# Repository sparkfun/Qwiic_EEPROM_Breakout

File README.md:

Qwiic EEPROM - 512Kbit
=======================================

[*Qwiic EEPROM - 512Kbit (COM-18355)*](https://www.sparkfun.com/products/18355)

A simple breakout for the 512kbit common I2C EEPROMs.

Repository Contents
-------------------

* **/Hardware** - Eagle design files (.brd, .sch)
* **/Firmware** - EEPROM test sketch

Documentation
------------

* **[SparkFun External EEPROM Arduino Library](https://github.com/sparkfun/SparkFun_External_EEPROM_Arduino_Library)** - Arduino library for the Qwiic EEPROM - 512Kbit
* **[Qwiic EEPROM Python Package](https://github.com/sparkfun/Qwiic_EEPROM_Py)** - Python package for the Qwiic EEPROM - 512Kbit
* **[Datasheet CAT24C512](https://www.onsemi.com/pub/Collateral/CAT24C512-D.PDF)** - Datasheet for EEPROM part number 24512A
<!-- * **[Datasheet RM24C512C](https://cdn.sparkfun.com/assets/2/c/4/c/0/DS-RM24C512C_082.pdf)** - Datasheet for EEPROM part number 24512C -->
* **[Reading and Writing Serial EEPROMs](https://learn.sparkfun.com/tutorials/reading-and-writing-serial-eeproms)** - Tutorial
* **[Qwiic EEPROM Hookup Guide](https://learn.sparkfun.com/tutorials/1661)** - Hookup guide for the Qwiic EEPROM - 512Kbit

License Information
-------------------

This product is _**open source**_! 

Please review the LICENSE.md file for license information. 

If you have any questions or concerns on licensing, please contact technical support on our [SparkFun forums](https://forum.sparkfun.com/viewforum.php?f=152).

Distributed as-is; no warranty is given.

- Your friends at SparkFun.

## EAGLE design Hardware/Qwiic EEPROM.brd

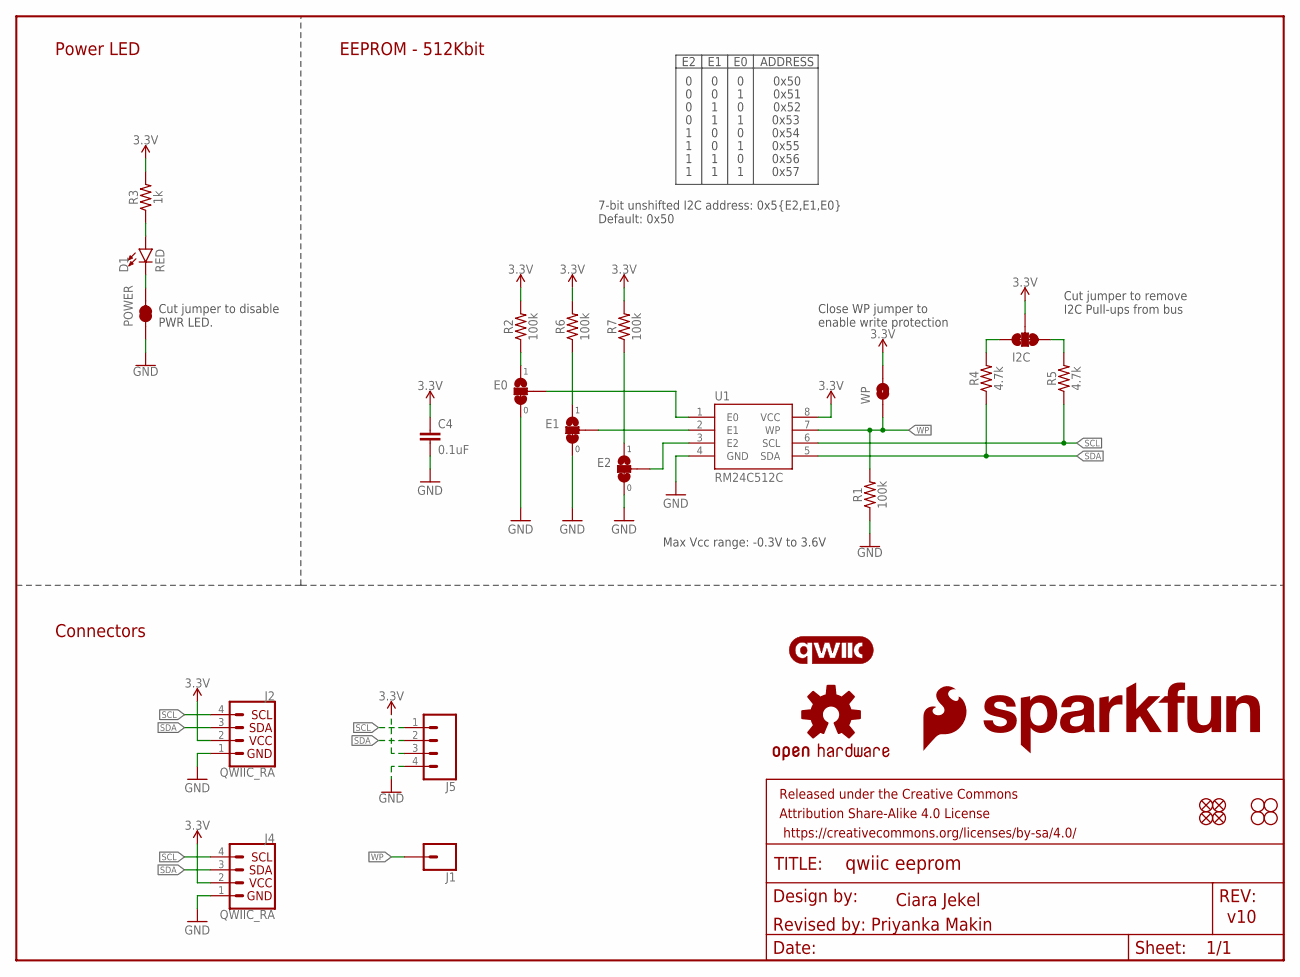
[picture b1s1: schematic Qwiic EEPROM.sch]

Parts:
C4: 0.1uF; 0603
D1: RED; LED-0603
E0, E1, E2: JUMPER-SMT_3_1-NC_TRACE_SILK; SMT-JUMPER_3_1-NC_TRACE_SILK
FRAME1: FRAME-LETTER; CREATIVE_COMMONS
I2C: JUMPER-SMT_3_2-NC_TRACE_SILK; SMT-JUMPER_3_2-NC_TRACE_SILK
J1: CONN_01PTH_NO_SILK_YES_STOP; 1X01_NO_SILK
J2, J4: QWIIC_RA; JST04_1MM_RA
J5: CONN_041X04_NO_SILK_NO_POP; 1X04_NO_SILK
JP1, JP2, JP5, JP6: FIDUCIALUFIDUCIAL; FIDUCIAL-MICRO
JP3, JP4, JP7, JP8: STAND-OFF
LOGO1: OSHW-LOGOMINI; OSHW-LOGO-MINI
LOGO2: SFE_LOGO_NAME.1_INCH; SFE_LOGO_NAME_.1
LOGO3: SFE_LOGO_FLAME.1_INCH; SFE_LOGO_FLAME_.1
LOGO4: QWIIC_LOGO_4MM; QWIIC_4MM
POWER: JUMPER-SMT_2_NC_TRACE_SILK; SMT-JUMPER_2_NC_TRACE_SILK
R1, R2, R6, R7: 100k; 0603
R3: 1k; 0603
R4, R5: 4.7k; 0603
U1: RM24C512C; SO08
WP: JUMPER-SMT_2_NO_SILK; SMT-JUMPER_2_NO_SILK

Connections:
3.3V: C4.1, I2C.2, J2.2, J4.2, J5.3, R2.2, R3.2, R6.2, R7.2, U1.8 (VCC), WP.2
GND: C4.2, E0.3, E1.3, E2.3, J2.1, J4.1, J5.4, POWER.1, R1.1, U1.4 (GND)
unnamed: I2C.1, R5.2
unnamed: I2C.3, R4.2
unnamed: D1.A, R3.1
unnamed: E2.2, U1.3 (E2)
unnamed: E1.2, U1.2 (E1)
unnamed: E0.2, U1.1 (E0)
unnamed: E0.1, R2.1
unnamed: E2.1, R7.1
unnamed: E1.1, R6.1
unnamed: D1.C, POWER.2
SCL: J2.4, J4.4, J5.1, R5.1, U1.6 (SCL)
SDA: J2.3, J4.3, J5.2, R4.1, U1.5 (SDA)
WP: J1.1, R1.2, U1.7 (WP), WP.1

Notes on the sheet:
Ciara Jekel
v10
7-bit unshifted I2C address: 0x5{E2,E1,E0} Default: 0x50
Cut jumper to remove I2C Pull-ups from bus
Close WP jumper to enable write protection
ADDRESS
0x50
0x51
0x52
0x53
0x54
0x55
0x56
0x57
Revised by: Priyanka Makin
Power LED
EEPROM - 512Kbit
Connectors
Max Vcc range: -0.3V to 3.6V
Cut jumper to disable PWR LED.

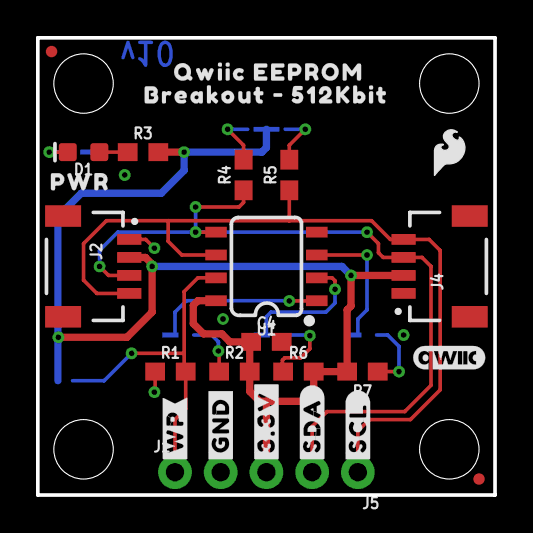
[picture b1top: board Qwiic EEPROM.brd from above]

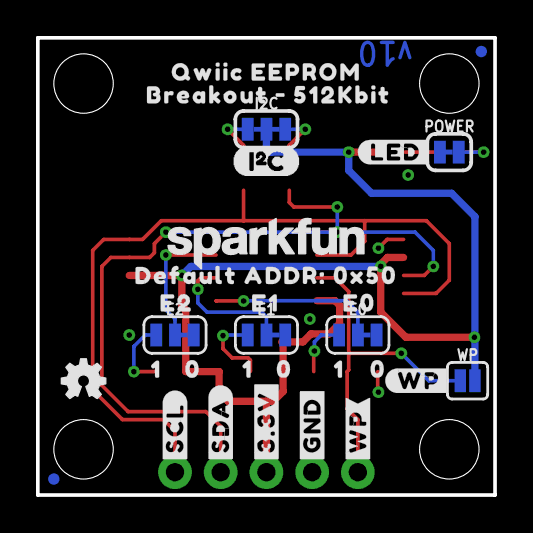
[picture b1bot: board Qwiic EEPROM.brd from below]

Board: 2 copper layers, 25.4 x 25.4 mm, 61 parts (30 on the bottom side), 15 nets.

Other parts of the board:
U$1, U$2: #WP#3
U$3: #WP#0
U$4: E00
U$5: E10
U$6: E20
U$7, U$8, U$9: 00
U$10, U$14: #GND#0
U$11: (I_SUPER2_C)
U$12: PWR0
U$13, U$21, U$22: 10
U$15, U$16: #3#3V#0
U$17, U$29: #SDA#0
U$18: #LED#2
U$19, U$20: QWIIC_EEPROM0
U$23, U$24: BREAKOUT_#_512KBIT0
U$25: DEFAULT_ADDR#_0X500
U$30, U$31: #SCL#0

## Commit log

2021-05-26 Add datasheet, make sure all parts are from SF libraries
2021-05-26 Hardware updates
    Schematic symbols from current SF libs
    Added mounting holes
    re-routing
    Update 3.3V rail width
2021-05-26 Vectorize labels
2021-05-28 Design review changes
    Schematic:
    * Added Vcc range for EEPROM IC
    * Updated notes for power led and address jumpers
    * Got rid of legacy font
    * Replaced pullup/pulldown resistors R1, R2, R6, R7 to 100k
    Board:
2021-06-02 QC Double-check
2021-06-02 QC Double-check: update silkscreen
2021-06-02 Update WP buzzard label
2021-06-02 Panelize
2021-07-27 Update README.md
    Update pic and documentation links
2021-07-27 Update README.md
    Fix formatting from commented out line
2022-02-28 Update EEPROM part number to CAT24C51 and re-generate schematic

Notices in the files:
parts and their libraries:
SparkFun-Resistors: Licensing: Creative Commons ShareAlike 4.0 International - https://creativecommons.org/licenses/by-sa/4.0
SparkFun-Aesthetics: Released under the Creative Commons Attribution Share-Alike 4.0 License
SparkFun-Aesthetics: https://creativecommons.org/licenses/by-sa/4.0
